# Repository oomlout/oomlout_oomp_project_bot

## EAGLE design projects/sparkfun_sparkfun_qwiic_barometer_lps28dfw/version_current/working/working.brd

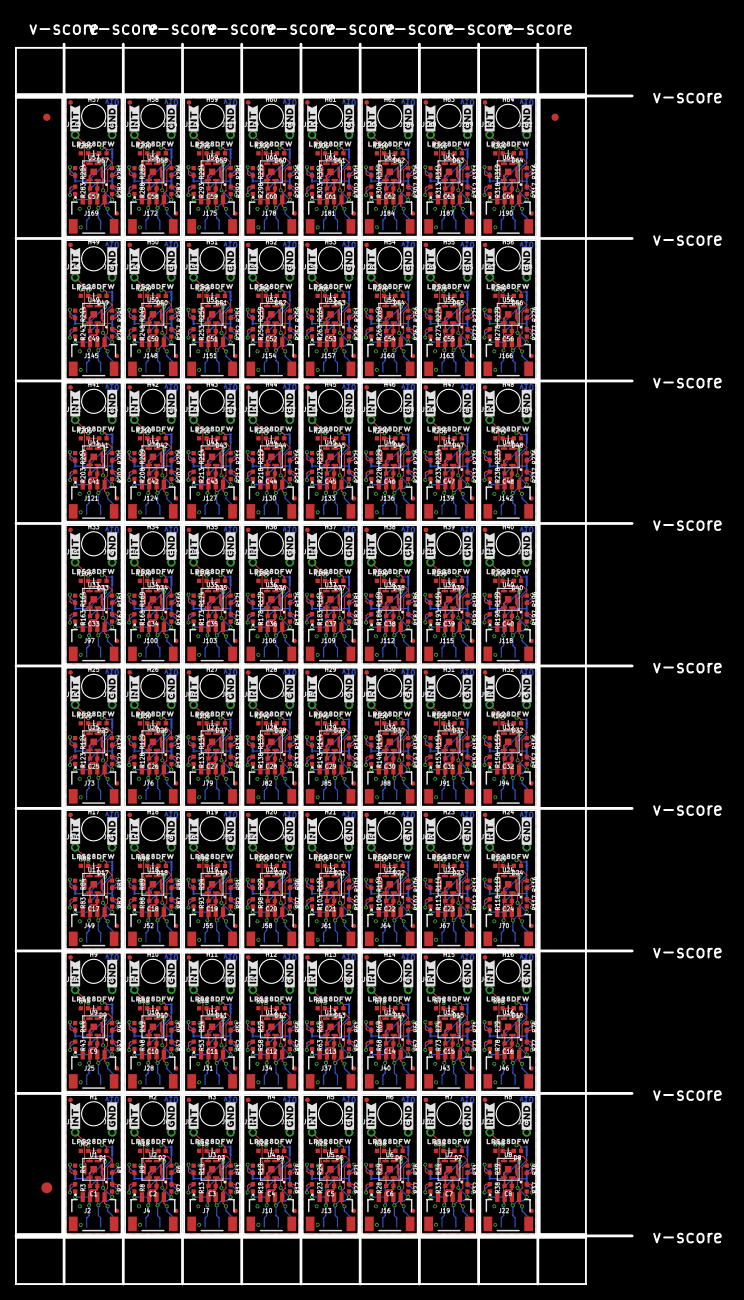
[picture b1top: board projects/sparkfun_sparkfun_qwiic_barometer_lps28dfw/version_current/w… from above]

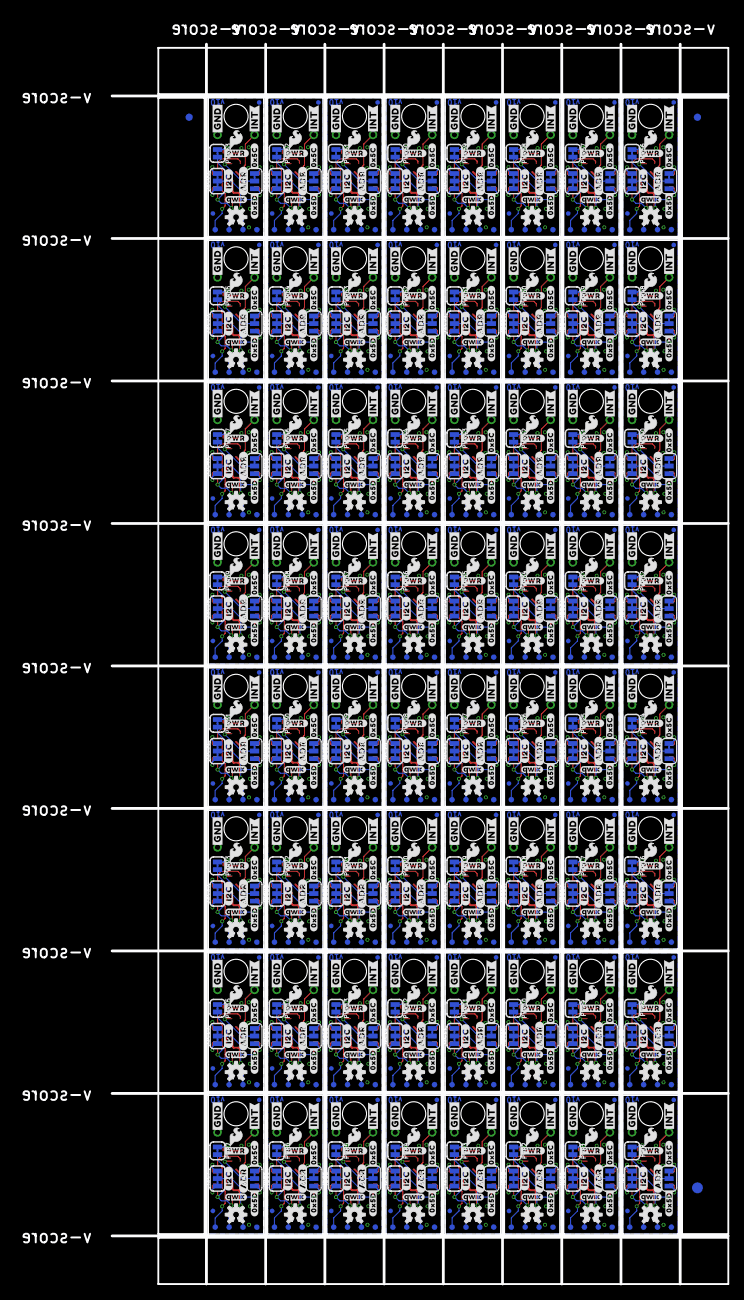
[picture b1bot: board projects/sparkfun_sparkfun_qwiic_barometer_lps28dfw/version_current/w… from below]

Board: 2 copper layers, 84.6 x 170.2 mm, 2438 parts (1219 on the bottom side), 768 nets.

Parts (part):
ADR, ADR1, ADR2, ADR3, ADR4, ADR5, ADR6, ADR7, ADR8, ADR9, ADR10, ADR11, ADR12, ADR13, ADR14, ADR15, ADR16, ADR17, ADR18, ADR19, ADR20, ADR21, ADR22, ADR23, ADR24, ADR25, ADR26, ADR27, ADR28, ADR29, ADR30, ADR31, ADR32, ADR33, ADR34, ADR35, ADR36, ADR37, ADR38, ADR39, ADR40, ADR41, ADR42, ADR43, ADR44, ADR45, ADR46, ADR47, ADR48, ADR49, ADR50, ADR51, ADR52, ADR53, ADR54, ADR55, ADR56, ADR57, ADR58, ADR59, ADR60, ADR61, ADR62, ADR63: JUMPER-SMT_3_1-NC_TRACE_SILK; SMT-JUMPER_3_1-NC_TRACE_SILK
C1, C2, C3, C4, C5, C6, C7, C8, C9, C10, C11, C12, C13, C14, C15, C16, C17, C18, C19, C20, C21, C22, C23, C24, C25, C26, C27, C28, C29, C30, C31, C32, C33, C34, C35, C36, C37, C38, C39, C40, C41, C42, C43, C44, C45, C46, C47, C48, C49, C50, C51, C52, C53, C54, C55, C56, C57, C58, C59, C60, C61, C62, C63, C64: 0.1uF; 0402-TIGHT
D1, D2, D3, D4, D5, D6, D7, D8, D9, D10, D11, D12, D13, D14, D15, D16, D17, D18, D19, D20, D21, D22, D23, D24, D25, D26, D27, D28, D29, D30, D31, D32, D33, D34, D35, D36, D37, D38, D39, D40, D41, D42, D43, D44, D45, D46, D47, D48, D49, D50, D51, D52, D53, D54, D55, D56, D57, D58, D59, D60, D61, D62, D63, D64: RED; LED-0402
E$1, E$2, E$3, E$4: FIDUCIAL-1X2
E$5, E$6: FIDUCIAL-1.5X3
FD1, FD2, FD3, FD4, FD5, FD6, FD7, FD8, FD9, FD10, FD11, FD12, FD13, FD14, FD15, FD16, FD17, FD18, FD19, FD20, FD21, FD22, FD23, FD24, FD25, FD26, FD27, FD28, FD29, FD30, FD31, FD32, FD33, FD34, FD35, FD36, FD37, FD38, FD39, FD40, FD41, FD42, FD43, FD44, FD45, FD46, FD47, FD48, FD49, FD50, FD51, FD52, FD53, FD54, FD55, FD56, FD57, FD58, FD59, FD60, FD61, FD62, FD63, FD64, FD65, FD66, FD67, FD68, FD69, FD70, FD71, FD72, FD73, FD74, FD75, FD76, FD77, FD78, FD79, FD80, FD81, FD82, FD83, FD84, FD85, FD86, FD87, FD88, FD89, FD90, FD91, FD92, FD93, FD94, FD95, FD96, FD97, FD98, FD99, FD100, FD101, FD102, FD103, FD104, FD105, FD106, FD107, FD108, FD109, FD110, FD111, FD112, FD113, FD114, FD115, FD116, FD117, FD118, FD119, FD120, FD121, FD122, FD123, FD124, FD125, FD126, FD127, FD128, FD129, FD130, FD131, FD132, FD133, FD134, FD135, FD136, FD137, FD138, FD139, FD140, FD141, FD142, FD143, FD144, FD145, FD146, FD147, FD148, FD149, FD150, FD151, FD152, FD153, FD154, FD155, FD156, FD157, FD158, FD159, FD160, FD161, FD162, FD163, FD164, FD165, FD166, FD167, FD168, FD169, FD170, FD171, FD172, FD173, FD174, FD175, FD176, FD177, FD178, FD179, FD180, FD181, FD182, FD183, FD184, FD185, FD186, FD187, FD188, FD189, FD190, FD191, FD192, FD193, FD194, FD195, FD196, FD197, FD198, FD199, FD200, FD201, FD202, FD203, FD204, FD205, FD206, FD207, FD208, FD209, FD210, FD211, FD212, FD213, FD214, FD215, FD216, FD217, FD218, FD219, FD220, FD221, FD222, FD223, FD224, FD225, FD226, FD227, FD228, FD229, FD230, FD231, FD232, FD233, FD234, FD235, FD236, FD237, FD238, FD239, FD240, FD241, FD242, FD243, FD244, FD245, FD246, FD247, FD248, FD249, FD250, FD251, FD252, FD253, FD254, FD255, FD256: FIDUCIALUFIDUCIAL; FIDUCIAL-MICRO
FRAME1, FRAME2, FRAME3, FRAME4, FRAME5, FRAME6, FRAME7, FRAME8, FRAME9, FRAME10, FRAME11, FRAME12, FRAME13, FRAME14, FRAME15, FRAME16, FRAME17, FRAME18, FRAME19, FRAME20, FRAME21, FRAME22, FRAME23, FRAME24, FRAME25, FRAME26, FRAME27, FRAME28, FRAME29, FRAME30, FRAME31, FRAME32, FRAME33, FRAME34, FRAME35, FRAME36, FRAME37, FRAME38, FRAME39, FRAME40, FRAME41, FRAME42, FRAME43, FRAME44, FRAME45, FRAME46, FRAME47, FRAME48, FRAME49, FRAME50, FRAME51, FRAME52, FRAME53, FRAME54, FRAME55, FRAME56, FRAME57, FRAME58, FRAME59, FRAME60, FRAME61, FRAME62, FRAME63, FRAME64: FRAME-LETTER; CREATIVE_COMMONS
H1, H2, H3, H4, H5, H6, H7, H8, H9, H10, H11, H12, H13, H14, H15, H16, H17, H18, H19, H20, H21, H22, H23, H24, H25, H26, H27, H28, H29, H30, H31, H32, H33, H34, H35, H36, H37, H38, H39, H40, H41, H42, H43, H44, H45, H46, H47, H48, H49, H50, H51, H52, H53, H54, H55, H56, H57, H58, H59, H60, H61, H62, H63, H64: STAND-OFF
I2C, I2C1, I2C2, I2C3, I2C4, I2C5, I2C6, I2C7, I2C8, I2C9, I2C10, I2C11, I2C12, I2C13, I2C14, I2C15, I2C16, I2C17, I2C18, I2C19, I2C20, I2C21, I2C22, I2C23, I2C24, I2C25, I2C26, I2C27, I2C28, I2C29, I2C30, I2C31, I2C32, I2C33, I2C34, I2C35, I2C36, I2C37, I2C38, I2C39, I2C40, I2C41, I2C42, I2C43, I2C44, I2C45, I2C46, I2C47, I2C48, I2C49, I2C50, I2C51, I2C52, I2C53, I2C54, I2C55, I2C56, I2C57, I2C58, I2C59, I2C60, I2C61, I2C62, I2C63: JUMPER-SMT_3_2-NC_TRACE_SILK; SMT-JUMPER_3_2-NC_TRACE_SILK
J1, J3, J5, J6, J8, J9, J11, J12, J14, J15, J17, J18, J20, J21, J23, J24, J26, J27, J29, J30, J32, J33, J35, J36, J38, J39, J41, J42, J44, J45, J47, J48, J50, J51, J53, J54, J56, J57, J59, J60, J62, J63, J65, J66, J68, J69, J71, J72, J74, J75, J77, J78, J80, J81, J83, J84, J86, J87, J89, J90, J92, J93, J95, J96, J98, J99, J101, J102, J104, J105, J107, J108, J110, J111, J113, J114, J116, J117, J119, J120, J122, J123, J125, J126, J128, J129, J131, J132, J134, J135, J137, J138, J140, J141, J143, J144, J146, J147, J149, J150, J152, J153, J155, J156, J158, J159, J161, J162, J164, J165, J167, J168, J170, J171, J173, J174, J176, J177, J179, J180, J182, J183, J185, J186, J188, J189, J191, J192: 1X01_1MM_NO_SILK
J2, J4, J7, J10, J13, J16, J19, J22, J25, J28, J31, J34, J37, J40, J43, J46, J49, J52, J55, J58, J61, J64, J67, J70, J73, J76, J79, J82, J85, J88, J91, J94, J97, J100, J103, J106, J109, J112, J115, J118, J121, J124, J127, J130, J133, J136, J139, J142, J145, J148, J151, J154, J157, J160, J163, J166, J169, J172, J175, J178, J181, J184, J187, J190: QWIIC_RIGHT_ANGLE; JST04_1MM_RA
LOGO1, LOGO4, LOGO7, LOGO10, LOGO13, LOGO16, LOGO19, LOGO22, LOGO25, LOGO28, LOGO31, LOGO34, LOGO37, LOGO40, LOGO43, LOGO46, LOGO49, LOGO52, LOGO55, LOGO58, LOGO61, LOGO64, LOGO67, LOGO70, LOGO73, LOGO76, LOGO79, LOGO82, LOGO85, LOGO88, LOGO91, LOGO94, LOGO97, LOGO100, LOGO103, LOGO106, LOGO109, LOGO112, LOGO115, LOGO118, LOGO121, LOGO124, LOGO127, LOGO130, LOGO133, LOGO136, LOGO139, LOGO142, LOGO145, LOGO148, LOGO151, LOGO154, LOGO157, LOGO160, LOGO163, LOGO166, LOGO169, LOGO172, LOGO175, LOGO178, LOGO181, LOGO184, LOGO187, LOGO190: OSHW-LOGOS; OSHW-LOGO-S
LOGO2, LOGO5, LOGO8, LOGO11, LOGO14, LOGO17, LOGO20, LOGO23, LOGO26, LOGO29, LOGO32, LOGO35, LOGO38, LOGO41, LOGO44, LOGO47, LOGO50, LOGO53, LOGO56, LOGO59, LOGO62, LOGO65, LOGO68, LOGO71, LOGO74, LOGO77, LOGO80, LOGO83, LOGO86, LOGO89, LOGO92, LOGO95, LOGO98, LOGO101, LOGO104, LOGO107, LOGO110, LOGO113, LOGO116, LOGO119, LOGO122, LOGO125, LOGO128, LOGO131, LOGO134, LOGO137, LOGO140, LOGO143, LOGO146, LOGO149, LOGO152, LOGO155, LOGO158, LOGO161, LOGO164, LOGO167, LOGO170, LOGO173, LOGO176, LOGO179, LOGO182, LOGO185, LOGO188, LOGO191: QWIIC_LOGO_3MM; QWIIC_3MM
LOGO3, LOGO6, LOGO9, LOGO12, LOGO15, LOGO18, LOGO21, LOGO24, LOGO27, LOGO30, LOGO33, LOGO36, LOGO39, LOGO42, LOGO45, LOGO48, LOGO51, LOGO54, LOGO57, LOGO60, LOGO63, LOGO66, LOGO69, LOGO72, LOGO75, LOGO78, LOGO81, LOGO84, LOGO87, LOGO90, LOGO93, LOGO96, LOGO99, LOGO102, LOGO105, LOGO108, LOGO111, LOGO114, LOGO117, LOGO120, LOGO123, LOGO126, LOGO129, LOGO132, LOGO135, LOGO138, LOGO141, LOGO144, LOGO147, LOGO150, LOGO153, LOGO156, LOGO159, LOGO162, LOGO165, LOGO168, LOGO171, LOGO174, LOGO177, LOGO180, LOGO183, LOGO186, LOGO189, LOGO192: SFE_LOGO_NAME_FLAMEBLANK; BLANK
PWR, PWR1, PWR2, PWR3, PWR4, PWR5, PWR6, PWR7, PWR8, PWR9, PWR10, PWR11, PWR12, PWR13, PWR14, PWR15, PWR16, PWR17, PWR18, PWR19, PWR20, PWR21, PWR22, PWR23, PWR24, PWR25, PWR26, PWR27, PWR28, PWR29, PWR30, PWR31, PWR32, PWR33, PWR34, PWR35, PWR36, PWR37, PWR38, PWR39, PWR40, PWR41, PWR42, PWR43, PWR44, PWR45, PWR46, PWR47, PWR48, PWR49, PWR50, PWR51, PWR52, PWR53, PWR54, PWR55, PWR56, PWR57, PWR58, PWR59, PWR60, PWR61, PWR62, PWR63: JUMPER-SMT_2_NC_TRACE_SILK; SMT-JUMPER_2_NC_TRACE_SILK
R1, R2, R5, R6, R7, R10, R11, R12, R15, R16, R17, R20, R21, R22, R25, R26, R27, R30, R31, R32, R35, R36, R37, R40, R41, R42, R45, R46, R47, R50, R51, R52, R55, R56, R57, R60, R61, R62, R65, R66, R67, R70, R71, R72, R75, R76, R77, R80, R81, R82, R85, R86, R87, R90, R91, R92, R95, R96, R97, R100, R101, R102, R105, R106, R107, R110, R111, R112, R115, R116, R117, R120, R121, R122, R125, R126, R127, R130, R131, R132, R135, R136, R137, R140, R141, R142, R145, R146, R147, R150, R151, R152, R155, R156, R157, R160, R161, R162, R165, R166, R167, R170, R171, R172, R175, R176, R177, R180, R181, R182, R185, R186, R187, R190, R191, R192, R195, R196, R197, R200, R201, R202, R205, R206, R207, R210, R211, R212, R215, R216, R217, R220, R221, R222, R225, R226, R227, R230, R231, R232, R235, R236, R237, R240, R241, R242, R245, R246, R247, R250, R251, R252, R255, R256, R257, R260, R261, R262, R265, R266, R267, R270, R271, R272, R275, R276, R277, R280, R281, R282, R285, R286, R287, R290, R291, R292, R295, R296, R297, R300, R301, R302, R305, R306, R307, R310, R311, R312, R315, R316, R317, R320: 2.2k; 0402-TIGHT
R3, R4, R8, R9, R13, R14, R18, R19, R23, R24, R28, R29, R33, R34, R38, R39, R43, R44, R48, R49, R53, R54, R58, R59, R63, R64, R68, R69, R73, R74, R78, R79, R83, R84, R88, R89, R93, R94, R98, R99, R103, R104, R108, R109, R113, R114, R118, R119, R123, R124, R128, R129, R133, R134, R138, R139, R143, R144, R148, R149, R153, R154, R158, R159, R163, R164, R168, R169, R173, R174, R178, R179, R183, R184, R188, R189, R193, R194, R198, R199, R203, R204, R208, R209, R213, R214, R218, R219, R223, R224, R228, R229, R233, R234, R238, R239, R243, R244, R248, R249, R253, R254, R258, R259, R263, R264, R268, R269, R273, R274, R278, R279, R283, R284, R288, R289, R293, R294, R298, R299, R303, R304, R308, R309, R313, R314, R318, R319: 10k; 0402-TIGHT
TP1, TP2, TP3, TP4, TP5, TP6, TP7, TP8, TP9, TP10, TP11, TP12, TP13, TP14, TP15, TP16, TP17, TP18, TP19, TP20, TP21, TP22, TP23, TP24, TP25, TP26, TP27, TP28, TP29, TP30, TP31, TP32, TP33, TP34, TP35, TP36, TP37, TP38, TP39, TP40, TP41, TP42, TP43, TP44, TP45, TP46, TP47, TP48, TP49, TP50, TP51, TP52, TP53, TP54, TP55, TP56, TP57, TP58, TP59, TP60, TP61, TP62, TP63, TP64, TP65, TP66, TP67, TP68, TP69, TP70, TP71, TP72, TP73, TP74, TP75, TP76, TP77, TP78, TP79, TP80, TP81, TP82, TP83, TP84, TP85, TP86, TP87, TP88, TP89, TP90, TP91, TP92, TP93, TP94, TP95, TP96, TP97, TP98, TP99, TP100, TP101, TP102, TP103, TP104, TP105, TP106, TP107, TP108, TP109, TP110, TP111, TP112, TP113, TP114, TP115, TP116, TP117, TP118, TP119, TP120, TP121, TP122, TP123, TP124, TP125, TP126, TP127, TP128, TP129, TP130, TP131, TP132, TP133, TP134, TP135, TP136, TP137, TP138, TP139, TP140, TP141, TP142, TP143, TP144, TP145, TP146, TP147, TP148, TP149, TP150, TP151, TP152, TP153, TP154, TP155, TP156, TP157, TP158, TP159, TP160, TP161, TP162, TP163, TP164, TP165, TP166, TP167, TP168, TP169, TP170, TP171, TP172, TP173, TP174, TP175, TP176, TP177, TP178, TP179, TP180, TP181, TP182, TP183, TP184, TP185, TP186, TP187, TP188, TP189, TP190, TP191, TP192, TP193, TP194, TP195, TP196, TP197, TP198, TP199, TP200, TP201, TP202, TP203, TP204, TP205, TP206, TP207, TP208, TP209, TP210, TP211, TP212, TP213, TP214, TP215, TP216, TP217, TP218, TP219, TP220, TP221, TP222, TP223, TP224, TP225, TP226, TP227, TP228, TP229, TP230, TP231, TP232, TP233, TP234, TP235, TP236, TP237, TP238, TP239, TP240, TP241, TP242, TP243, TP244, TP245, TP246, TP247, TP248, TP249, TP250, TP251, TP252, TP253, TP254, TP255, TP256: TEST-POINT3; PAD.03X.03
U1, U2, U3, U4, U5, U6, U7, U8, U9, U10, U11, U12, U13, U14, U15, U16, U17, U18, U19, U20, U21, U22, U23, U24, U25, U26, U27, U28, U29, U30, U31, U32, U33, U34, U35, U36, U37, U38, U39, U40, U41, U42, U43, U44, U45, U46, U47, U48, U49, U50, U51, U52, U53, U54, U55, U56, U57, U58, U59, U60, U61, U62, U63, U64: LPS28DFW
U$1, U$3, U$15, U$19, U$28, U$30, U$39, U$41, U$50, U$52, U$61, U$63, U$72, U$74, U$83, U$85, U$94, U$96, U$105, U$107, U$116, U$118, U$127, U$129, U$138, U$140, U$149, U$151, U$160, U$162, U$171, U$173, U$182, U$184, U$193, U$195, U$204, U$206, U$215, U$217, U$226, U$228, U$237, U$239, U$248, U$250, U$259, U$261, U$270, U$272, U$281, U$283, U$292, U$294, U$303, U$305, U$314, U$316, U$325, U$327, U$336, U$338, U$347, U$349, U$358, U$360, U$369, U$371, U$380, U$382, U$391, U$393, U$402, U$404, U$413, U$415, U$424, U$426, U$435, U$437, U$446, U$448, U$457, U$459, U$468, U$470, U$479, U$481, U$490, U$492, U$501, U$503, U$512, U$514, U$523, U$525, U$534, U$536, U$545, U$547, U$556, U$558, U$567, U$569, U$578, U$580, U$589, U$591, U$600, U$602, U$611, U$613, U$622, U$624, U$633, U$635, U$644, U$646, U$655, U$657, U$666, U$668, U$677, U$679, U$688, U$690, U$699, U$701: #INT#0
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
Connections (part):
3.3V: C1.1, I2C.2, J2.2, PWR.2, R3.2, TP2.1, U1.6
3.3V1: C2.1, I2C1.2, J4.2, PWR1.2, R8.2, TP6.1, U2.6
3.3V2: C3.1, I2C2.2, J7.2, PWR2.2, R13.2, TP10.1, U3.6
3.3V3: C4.1, I2C3.2, J10.2, PWR3.2, R18.2, TP14.1, U4.6
3.3V4: C5.1, I2C4.2, J13.2, PWR4.2, R23.2, TP18.1, U5.6
3.3V5: C6.1, I2C5.2, J16.2, PWR5.2, R28.2, TP22.1, U6.6
3.3V6: C7.1, I2C6.2, J19.2, PWR6.2, R33.2, TP26.1, U7.6
3.3V7: C8.1, I2C7.2, J22.2, PWR7.2, R38.2, TP30.1, U8.6
3.3V8: C9.1, I2C8.2, J25.2, PWR8.2, R43.2, TP34.1, U9.6
3.3V9: C10.1, I2C9.2, J28.2, PWR9.2, R48.2, TP38.1, U10.6
3.3V10: C11.1, I2C10.2, J31.2, PWR10.2, R53.2, TP42.1, U11.6
3.3V11: C12.1, I2C11.2, J34.2, PWR11.2, R58.2, TP46.1, U12.6
3.3V12: C13.1, I2C12.2, J37.2, PWR12.2, R63.2, TP50.1, U13.6
3.3V13: C14.1, I2C13.2, J40.2, PWR13.2, R68.2, TP54.1, U14.6
3.3V14: C15.1, I2C14.2, J43.2, PWR14.2, R73.2, TP58.1, U15.6
3.3V15: C16.1, I2C15.2, J46.2, PWR15.2, R78.2, TP62.1, U16.6
3.3V16: C17.1, I2C16.2, J49.2, PWR16.2, R83.2, TP66.1, U17.6
3.3V17: C18.1, I2C17.2, J52.2, PWR17.2, R88.2, TP70.1, U18.6
3.3V18: C19.1, I2C18.2, J55.2, PWR18.2, R93.2, TP74.1, U19.6
3.3V19: C20.1, I2C19.2, J58.2, PWR19.2, R98.2, TP78.1, U20.6
3.3V20: C21.1, I2C20.2, J61.2, PWR20.2, R103.2, TP82.1, U21.6
3.3V21: C22.1, I2C21.2, J64.2, PWR21.2, R108.2, TP86.1, U22.6
3.3V22: C23.1, I2C22.2, J67.2, PWR22.2, R113.2, TP90.1, U23.6
3.3V23: C24.1, I2C23.2, J70.2, PWR23.2, R118.2, TP94.1, U24.6
3.3V24: C25.1, I2C24.2, J73.2, PWR24.2, R123.2, TP98.1, U25.6
3.3V25: C26.1, I2C25.2, J76.2, PWR25.2, R128.2, TP102.1, U26.6
3.3V26: C27.1, I2C26.2, J79.2, PWR26.2, R133.2, TP106.1, U27.6
3.3V27: C28.1, I2C27.2, J82.2, PWR27.2, R138.2, TP110.1, U28.6
3.3V28: C29.1, I2C28.2, J85.2, PWR28.2, R143.2, TP114.1, U29.6
3.3V29: C30.1, I2C29.2, J88.2, PWR29.2, R148.2, TP118.1, U30.6
3.3V30: C31.1, I2C30.2, J91.2, PWR30.2, R153.2, TP122.1, U31.6
3.3V31: C32.1, I2C31.2, J94.2, PWR31.2, R158.2, TP126.1, U32.6
3.3V32: C33.1, I2C32.2, J97.2, PWR32.2, R163.2, TP130.1, U33.6
3.3V33: C34.1, I2C33.2, J100.2, PWR33.2, R168.2, TP134.1, U34.6
3.3V34: C35.1, I2C34.2, J103.2, PWR34.2, R173.2, TP138.1, U35.6
3.3V35: C36.1, I2C35.2, J106.2, PWR35.2, R178.2, TP142.1, U36.6
3.3V36: C37.1, I2C36.2, J109.2, PWR36.2, R183.2, TP146.1, U37.6
3.3V37: C38.1, I2C37.2, J112.2, PWR37.2, R188.2, TP150.1, U38.6
3.3V38: C39.1, I2C38.2, J115.2, PWR38.2, R193.2, TP154.1, U39.6
3.3V39: C40.1, I2C39.2, J118.2, PWR39.2, R198.2, TP158.1, U40.6
3.3V40: C41.1, I2C40.2, J121.2, PWR40.2, R203.2, TP162.1, U41.6
3.3V41: C42.1, I2C41.2, J124.2, PWR41.2, R208.2, TP166.1, U42.6
3.3V42: C43.1, I2C42.2, J127.2, PWR42.2, R213.2, TP170.1, U43.6
3.3V43: C44.1, I2C43.2, J130.2, PWR43.2, R218.2, TP174.1, U44.6
3.3V44: C45.1, I2C44.2, J133.2, PWR44.2, R223.2, TP178.1, U45.6
3.3V45: C46.1, I2C45.2, J136.2, PWR45.2, R228.2, TP182.1, U46.6
3.3V46: C47.1, I2C46.2, J139.2, PWR46.2, R233.2, TP186.1, U47.6
3.3V47: C48.1, I2C47.2, J142.2, PWR47.2, R238.2, TP190.1, U48.6
3.3V48: C49.1, I2C48.2, J145.2, PWR48.2, R243.2, TP194.1, U49.6
3.3V49: C50.1, I2C49.2, J148.2, PWR49.2, R248.2, TP198.1, U50.6
3.3V50: C51.1, I2C50.2, J151.2, PWR50.2, R253.2, TP202.1, U51.6
3.3V51: C52.1, I2C51.2, J154.2, PWR51.2, R258.2, TP206.1, U52.6
3.3V52: C53.1, I2C52.2, J157.2, PWR52.2, R263.2, TP210.1, U53.6
3.3V53: C54.1, I2C53.2, J160.2, PWR53.2, R268.2, TP214.1, U54.6
3.3V54: C55.1, I2C54.2, J163.2, PWR54.2, R273.2, TP218.1, U55.6
3.3V55: C56.1, I2C55.2, J166.2, PWR55.2, R278.2, TP222.1, U56.6
3.3V56: C57.1, I2C56.2, J169.2, PWR56.2, R283.2, TP226.1, U57.6
3.3V57: C58.1, I2C57.2, J172.2, PWR57.2, R288.2, TP230.1, U58.6
3.3V58: C59.1, I2C58.2, J175.2, PWR58.2, R293.2, TP234.1, U59.6
3.3V59: C60.1, I2C59.2, J178.2, PWR59.2, R298.2, TP238.1, U60.6
3.3V60: C61.1, I2C60.2, J181.2, PWR60.2, R303.2, TP242.1, U61.6
3.3V61: C62.1, I2C61.2, J184.2, PWR61.2, R308.2, TP246.1, U62.6
3.3V62: C63.1, I2C62.2, J187.2, PWR62.2, R313.2, TP250.1, U63.6
3.3V63: C64.1, I2C63.2, J190.2, PWR63.2, R318.2, TP254.1, U64.6
ADR: ADR.2, U1.2
ADR1: ADR1.2, U2.2
ADR2: ADR2.2, U3.2
ADR3: ADR3.2, U4.2
ADR4: ADR4.2, U5.2
ADR5: ADR5.2, U6.2
ADR6: ADR6.2, U7.2
ADR7: ADR7.2, U8.2
ADR8: ADR8.2, U9.2
ADR9: ADR9.2, U10.2
ADR10: ADR10.2, U11.2
ADR11: ADR11.2, U12.2
ADR12: ADR12.2, U13.2
ADR13: ADR13.2, U14.2
ADR14: ADR14.2, U15.2
ADR15: ADR15.2, U16.2
ADR16: ADR16.2, U17.2
ADR17: ADR17.2, U18.2
ADR18: ADR18.2, U19.2
ADR19: ADR19.2, U20.2
ADR20: ADR20.2, U21.2
ADR21: ADR21.2, U22.2
ADR22: ADR22.2, U23.2
ADR23: ADR23.2, U24.2
ADR24: ADR24.2, U25.2
ADR25: ADR25.2, U26.2
ADR26: ADR26.2, U27.2
ADR27: ADR27.2, U28.2
ADR28: ADR28.2, U29.2
ADR29: ADR29.2, U30.2
ADR30: ADR30.2, U31.2
ADR31: ADR31.2, U32.2
ADR32: ADR32.2, U33.2
ADR33: ADR33.2, U34.2
ADR34: ADR34.2, U35.2
ADR35: ADR35.2, U36.2
ADR36: ADR36.2, U37.2
ADR37: ADR37.2, U38.2
ADR38: ADR38.2, U39.2
ADR39: ADR39.2, U40.2
ADR40: ADR40.2, U41.2
ADR41: ADR41.2, U42.2
ADR42: ADR42.2, U43.2
ADR43: ADR43.2, U44.2
ADR44: ADR44.2, U45.2
ADR45: ADR45.2, U46.2
ADR46: ADR46.2, U47.2
ADR47: ADR47.2, U48.2
ADR48: ADR48.2, U49.2
ADR49: ADR49.2, U50.2
ADR50: ADR50.2, U51.2
ADR51: ADR51.2, U52.2
ADR52: ADR52.2, U53.2
ADR53: ADR53.2, U54.2
ADR54: ADR54.2, U55.2
ADR55: ADR55.2, U56.2
ADR56: ADR56.2, U57.2
ADR57: ADR57.2, U58.2
ADR58: ADR58.2, U59.2
ADR59: ADR59.2, U60.2
ADR60: ADR60.2, U61.2
ADR61: ADR61.2, U62.2
ADR62: ADR62.2, U63.2
ADR63: ADR63.2, U64.2
GND: C1.2, J1.1, J2.1, R4.1, R5.1, TP1.1, U1.5, U1.7
GND1: C2.2, J4.1, J6.1, R9.1, R10.1, TP5.1, U2.5, U2.7
GND2: C3.2, J7.1, J9.1, R14.1, R15.1, TP9.1, U3.5, U3.7
GND3: C4.2, J10.1, J12.1, R19.1, R20.1, TP13.1, U4.5, U4.7
GND4: C5.2, J13.1, J15.1, R24.1, R25.1, TP17.1, U5.5, U5.7
GND5: C6.2, J16.1, J18.1, R29.1, R30.1, TP21.1, U6.5, U6.7
GND6: C7.2, J19.1, J21.1, R34.1, R35.1, TP25.1, U7.5, U7.7
GND7: C8.2, J22.1, J24.1, R39.1, R40.1, TP29.1, U8.5, U8.7
GND8: C9.2, J25.1, J27.1, R44.1, R45.1, TP33.1, U9.5, U9.7
GND9: C10.2, J28.1, J30.1, R49.1, R50.1, TP37.1, U10.5, U10.7
GND10: C11.2, J31.1, J33.1, R54.1, R55.1, TP41.1, U11.5, U11.7
GND11: C12.2, J34.1, J36.1, R59.1, R60.1, TP45.1, U12.5, U12.7
GND12: C13.2, J37.1, J39.1, R64.1, R65.1, TP49.1, U13.5, U13.7
GND13: C14.2, J40.1, J42.1, R69.1, R70.1, TP53.1, U14.5, U14.7
GND14: C15.2, J43.1, J45.1, R74.1, R75.1, TP57.1, U15.5, U15.7
GND15: C16.2, J46.1, J48.1, R79.1, R80.1, TP61.1, U16.5, U16.7
GND16: C17.2, J49.1, J51.1, R84.1, R85.1, TP65.1, U17.5, U17.7
GND17: C18.2, J52.1, J54.1, R89.1, R90.1, TP69.1, U18.5, U18.7
GND18: C19.2, J55.1, J57.1, R94.1, R95.1, TP73.1, U19.5, U19.7
GND19: C20.2, J58.1, J60.1, R99.1, R100.1, TP77.1, U20.5, U20.7
GND20: C21.2, J61.1, J63.1, R104.1, R105.1, TP81.1, U21.5, U21.7
GND21: C22.2, J64.1, J66.1, R109.1, R110.1, TP85.1, U22.5, U22.7
GND22: C23.2, J67.1, J69.1, R114.1, R115.1, TP89.1, U23.5, U23.7
GND23: C24.2, J70.1, J72.1, R119.1, R120.1, TP93.1, U24.5, U24.7
GND24: C25.2, J73.1, J75.1, R124.1, R125.1, TP97.1, U25.5, U25.7
GND25: C26.2, J76.1, J78.1, R129.1, R130.1, TP101.1, U26.5, U26.7
GND26: C27.2, J79.1, J81.1, R134.1, R135.1, TP105.1, U27.5, U27.7
GND27: C28.2, J82.1, J84.1, R139.1, R140.1, TP109.1, U28.5, U28.7
GND28: C29.2, J85.1, J87.1, R144.1, R145.1, TP113.1, U29.5, U29.7
GND29: C30.2, J88.1, J90.1, R149.1, R150.1, TP117.1, U30.5, U30.7
GND30: C31.2, J91.1, J93.1, R154.1, R155.1, TP121.1, U31.5, U31.7
GND31: C32.2, J94.1, J96.1, R159.1, R160.1, TP125.1, U32.5, U32.7
GND32: C33.2, J97.1, J99.1, R164.1, R165.1, TP129.1, U33.5, U33.7
GND33: C34.2, J100.1, J102.1, R169.1, R170.1, TP133.1, U34.5, U34.7
GND34: C35.2, J103.1, J105.1, R174.1, R175.1, TP137.1, U35.5, U35.7
GND35: C36.2, J106.1, J108.1, R179.1, R180.1, TP141.1, U36.5, U36.7
GND36: C37.2, J109.1, J111.1, R184.1, R185.1, TP145.1, U37.5, U37.7
GND37: C38.2, J112.1, J114.1, R189.1, R190.1, TP149.1, U38.5, U38.7
GND38: C39.2, J115.1, J117.1, R194.1, R195.1, TP153.1, U39.5, U39.7
GND39: C40.2, J118.1, J120.1, R199.1, R200.1, TP157.1, U40.5, U40.7
GND40: C41.2, J121.1, J123.1, R204.1, R205.1, TP161.1, U41.5, U41.7
GND41: C42.2, J124.1, J126.1, R209.1, R210.1, TP165.1, U42.5, U42.7
GND42: C43.2, J127.1, J129.1, R214.1, R215.1, TP169.1, U43.5, U43.7
GND43: C44.2, J130.1, J132.1, R219.1, R220.1, TP173.1, U44.5, U44.7
GND44: C45.2, J133.1, J135.1, R224.1, R225.1, TP177.1, U45.5, U45.7
GND45: C46.2, J136.1, J138.1, R229.1, R230.1, TP181.1, U46.5, U46.7
GND46: C47.2, J139.1, J141.1, R234.1, R235.1, TP185.1, U47.5, U47.7
GND47: C48.2, J142.1, J144.1, R239.1, R240.1, TP189.1, U48.5, U48.7
GND48: C49.2, J145.1, J147.1, R244.1, R245.1, TP193.1, U49.5, U49.7
GND49: C50.2, J148.1, J150.1, R249.1, R250.1, TP197.1, U50.5, U50.7
GND50: C51.2, J151.1, J153.1, R254.1, R255.1, TP201.1, U51.5, U51.7
GND51: C52.2, J154.1, J156.1, R259.1, R260.1, TP205.1, U52.5, U52.7
GND52: C53.2, J157.1, J159.1, R264.1, R265.1, TP209.1, U53.5, U53.7
GND53: C54.2, J160.1, J162.1, R269.1, R270.1, TP213.1, U54.5, U54.7
GND54: C55.2, J163.1, J165.1, R274.1, R275.1, TP217.1, U55.5, U55.7
GND55: C56.2, J166.1, J168.1, R279.1, R280.1, TP221.1, U56.5, U56.7
GND56: C57.2, J169.1, J171.1, R284.1, R285.1, TP225.1, U57.5, U57.7
GND57: C58.2, J172.1, J174.1, R289.1, R290.1, TP229.1, U58.5, U58.7
GND58: C59.2, J175.1, J177.1, R294.1, R295.1, TP233.1, U59.5, U59.7
GND59: C60.2, J178.1, J180.1, R299.1, R300.1, TP237.1, U60.5, U60.7
GND60: C61.2, J181.1, J183.1, R304.1, R305.1, TP241.1, U61.5, U61.7
GND61: C62.2, J184.1, J186.1, R309.1, R310.1, TP245.1, U62.5, U62.7
GND62: C63.2, J187.1, J189.1, R314.1, R315.1, TP249.1, U63.5, U63.7
GND63: C64.2, J190.1, J192.1, R319.1, R320.1, TP253.1, U64.5, U64.7
INT: J3.1, U1.4
INT1: J5.1, U2.4
INT2: J8.1, U3.4
INT3: J11.1, U4.4
INT4: J14.1, U5.4
INT5: J17.1, U6.4
INT6: J20.1, U7.4
INT7: J23.1, U8.4
INT8: J26.1, U9.4
INT9: J29.1, U10.4
INT10: J32.1, U11.4
INT11: J35.1, U12.4
INT12: J38.1, U13.4
INT13: J41.1, U14.4
INT14: J44.1, U15.4
INT15: J47.1, U16.4
INT16: J50.1, U17.4
INT17: J53.1, U18.4
INT18: J56.1, U19.4
INT19: J59.1, U20.4
INT20: J62.1, U21.4
INT21: J65.1, U22.4
INT22: J68.1, U23.4
INT23: J71.1, U24.4
INT24: J74.1, U25.4
INT25: J77.1, U26.4
INT26: J80.1, U27.4
INT27: J83.1, U28.4
INT28: J86.1, U29.4
INT29: J89.1, U30.4
INT30: J92.1, U31.4
INT31: J95.1, U32.4
INT32: J98.1, U33.4
INT33: J101.1, U34.4
INT34: J104.1, U35.4
INT35: J107.1, U36.4
INT36: J110.1, U37.4
INT37: J113.1, U38.4
INT38: J116.1, U39.4
INT39: J119.1, U40.4
INT40: J122.1, U41.4
INT41: J125.1, U42.4
INT42: J128.1, U43.4
INT43: J131.1, U44.4
INT44: J134.1, U45.4
INT45: J137.1, U46.4
INT46: J140.1, U47.4
INT47: J143.1, U48.4
INT48: J146.1, U49.4
INT49: J149.1, U50.4
INT50: J152.1, U51.4
INT51: J155.1, U52.4
INT52: J158.1, U53.4
INT53: J161.1, U54.4
INT54: J164.1, U55.4
INT55: J167.1, U56.4
INT56: J170.1, U57.4
INT57: J173.1, U58.4
INT58: J176.1, U59.4
INT59: J179.1, U60.4
INT60: J182.1, U61.4
INT61: J185.1, U62.4
INT62: J188.1, U63.4
INT63: J191.1, U64.4
unnamed: D1.C, R5.2
unnamed: I2C.3, R1.2
unnamed: I2C.1, R2.1
unnamed: D1.A, PWR.1
unnamed: ADR.3, R4.2
unnamed: ADR.1, R3.1
unnamed: I2C1.3, R6.2
unnamed: I2C1.1, R7.1
unnamed: ADR1.3, R9.2
unnamed: ADR1.1, R8.1
unnamed: D2.C, R10.2
unnamed: D2.A, PWR1.1
unnamed: I2C2.3, R11.2
unnamed: I2C2.1, R12.1
unnamed: ADR2.3, R14.2
unnamed: ADR2.1, R13.1
unnamed: D3.C, R15.2
unnamed: D3.A, PWR2.1
unnamed: I2C3.3, R16.2
unnamed: I2C3.1, R17.1
unnamed: ADR3.3, R19.2
unnamed: ADR3.1, R18.1
unnamed: D4.C, R20.2
unnamed: D4.A, PWR3.1
unnamed: I2C4.3, R21.2
unnamed: I2C4.1, R22.1
unnamed: ADR4.3, R24.2
unnamed: ADR4.1, R23.1
unnamed: D5.C, R25.2
unnamed: D5.A, PWR4.1
unnamed: I2C5.3, R26.2
unnamed: I2C5.1, R27.1
unnamed: ADR5.3, R29.2
unnamed: ADR5.1, R28.1
unnamed: D6.C, R30.2
unnamed: D6.A, PWR5.1
unnamed: I2C6.3, R31.2
unnamed: I2C6.1, R32.1
unnamed: ADR6.3, R34.2
unnamed: ADR6.1, R33.1
unnamed: D7.C, R35.2
unnamed: D7.A, PWR6.1
unnamed: I2C7.3, R36.2
unnamed: I2C7.1, R37.1
unnamed: ADR7.3, R39.2
unnamed: ADR7.1, R38.1
unnamed: D8.C, R40.2
unnamed: D8.A, PWR7.1
unnamed: I2C8.3, R41.2
unnamed: I2C8.1, R42.1
unnamed: ADR8.3, R44.2
unnamed: ADR8.1, R43.1
unnamed: D9.C, R45.2
unnamed: D9.A, PWR8.1
unnamed: I2C9.3, R46.2
unnamed: I2C9.1, R47.1
unnamed: ADR9.3, R49.2
unnamed: ADR9.1, R48.1
unnamed: D10.C, R50.2
unnamed: D10.A, PWR9.1
unnamed: I2C10.3, R51.2
unnamed: I2C10.1, R52.1
unnamed: ADR10.3, R54.2
unnamed: ADR10.1, R53.1
unnamed: D11.C, R55.2
unnamed: D11.A, PWR10.1
unnamed: I2C11.3, R56.2
unnamed: I2C11.1, R57.1
unnamed: ADR11.3, R59.2
unnamed: ADR11.1, R58.1
unnamed: D12.C, R60.2
unnamed: D12.A, PWR11.1
unnamed: I2C12.3, R61.2
unnamed: I2C12.1, R62.1
unnamed: ADR12.3, R64.2
unnamed: ADR12.1, R63.1
unnamed: D13.C, R65.2
unnamed: D13.A, PWR12.1
unnamed: I2C13.3, R66.2
unnamed: I2C13.1, R67.1
unnamed: ADR13.3, R69.2
unnamed: ADR13.1, R68.1
unnamed: D14.C, R70.2
unnamed: D14.A, PWR13.1
unnamed: I2C14.3, R71.2
unnamed: I2C14.1, R72.1
unnamed: ADR14.3, R74.2
unnamed: ADR14.1, R73.1
unnamed: D15.C, R75.2
unnamed: D15.A, PWR14.1
unnamed: I2C15.3, R76.2
unnamed: I2C15.1, R77.1
unnamed: ADR15.3, R79.2
unnamed: ADR15.1, R78.1
unnamed: D16.C, R80.2
unnamed: D16.A, PWR15.1
unnamed: I2C16.3, R81.2
unnamed: I2C16.1, R82.1
unnamed: ADR16.3, R84.2
unnamed: ADR16.1, R83.1
unnamed: D17.C, R85.2
unnamed: D17.A, PWR16.1
unnamed: I2C17.3, R86.2
unnamed: I2C17.1, R87.1
unnamed: ADR17.3, R89.2
unnamed: ADR17.1, R88.1
unnamed: D18.C, R90.2
unnamed: D18.A, PWR17.1
unnamed: I2C18.3, R91.2
unnamed: I2C18.1, R92.1
unnamed: ADR18.3, R94.2
unnamed: ADR18.1, R93.1
unnamed: D19.C, R95.2
unnamed: D19.A, PWR18.1
unnamed: I2C19.3, R96.2
unnamed: I2C19.1, R97.1
unnamed: ADR19.3, R99.2
unnamed: ADR19.1, R98.1
unnamed: D20.C, R100.2
unnamed: D20.A, PWR19.1
unnamed: I2C20.3, R101.2
unnamed: I2C20.1, R102.1
unnamed: ADR20.3, R104.2
unnamed: ADR20.1, R103.1
unnamed: D21.C, R105.2
unnamed: D21.A, PWR20.1
unnamed: I2C21.3, R106.2
unnamed: I2C21.1, R107.1
unnamed: ADR21.3, R109.2
unnamed: ADR21.1, R108.1
unnamed: D22.C, R110.2
unnamed: D22.A, PWR21.1
unnamed: I2C22.3, R111.2
unnamed: I2C22.1, R112.1
unnamed: ADR22.3, R114.2
unnamed: ADR22.1, R113.1
unnamed: D23.C, R115.2
unnamed: D23.A, PWR22.1
unnamed: I2C23.3, R116.2
unnamed: I2C23.1, R117.1
unnamed: ADR23.3, R119.2
unnamed: ADR23.1, R118.1
unnamed: D24.C, R120.2
unnamed: D24.A, PWR23.1
unnamed: I2C24.3, R121.2
unnamed: I2C24.1, R122.1
unnamed: ADR24.3, R124.2
unnamed: ADR24.1, R123.1
unnamed: D25.C, R125.2
unnamed: D25.A, PWR24.1
unnamed: I2C25.3, R126.2
unnamed: I2C25.1, R127.1
unnamed: ADR25.3, R129.2
unnamed: ADR25.1, R128.1
unnamed: D26.C, R130.2
unnamed: D26.A, PWR25.1
unnamed: I2C26.3, R131.2
unnamed: I2C26.1, R132.1
unnamed: ADR26.3, R134.2
unnamed: ADR26.1, R133.1
unnamed: D27.C, R135.2
unnamed: D27.A, PWR26.1
unnamed: I2C27.3, R136.2
unnamed: I2C27.1, R137.1
unnamed: ADR27.3, R139.2
unnamed: ADR27.1, R138.1
unnamed: D28.C, R140.2
unnamed: D28.A, PWR27.1
unnamed: I2C28.3, R141.2
unnamed: I2C28.1, R142.1
unnamed: ADR28.3, R144.2
unnamed: ADR28.1, R143.1
unnamed: D29.C, R145.2
unnamed: D29.A, PWR28.1
unnamed: I2C29.3, R146.2
unnamed: I2C29.1, R147.1
unnamed: ADR29.3, R149.2
unnamed: ADR29.1, R148.1
unnamed: D30.C, R150.2
unnamed: D30.A, PWR29.1
unnamed: I2C30.3, R151.2
unnamed: I2C30.1, R152.1
unnamed: ADR30.3, R154.2
unnamed: ADR30.1, R153.1
unnamed: D31.C, R155.2
unnamed: D31.A, PWR30.1
unnamed: I2C31.3, R156.2
unnamed: I2C31.1, R157.1
unnamed: ADR31.3, R159.2
unnamed: ADR31.1, R158.1
unnamed: D32.C, R160.2
unnamed: D32.A, PWR31.1
unnamed: I2C32.3, R161.2
unnamed: I2C32.1, R162.1
unnamed: ADR32.3, R164.2
unnamed: ADR32.1, R163.1
unnamed: D33.C, R165.2
unnamed: D33.A, PWR32.1
unnamed: I2C33.3, R166.2
unnamed: I2C33.1, R167.1
unnamed: ADR33.3, R169.2
unnamed: ADR33.1, R168.1
unnamed: D34.C, R170.2
unnamed: D34.A, PWR33.1
unnamed: I2C34.3, R171.2
unnamed: I2C34.1, R172.1
unnamed: ADR34.3, R174.2
unnamed: ADR34.1, R173.1
unnamed: D35.C, R175.2
unnamed: D35.A, PWR34.1
unnamed: I2C35.3, R176.2
unnamed: I2C35.1, R177.1
unnamed: ADR35.3, R179.2
unnamed: ADR35.1, R178.1
unnamed: D36.C, R180.2
unnamed: D36.A, PWR35.1
unnamed: I2C36.3, R181.2
unnamed: I2C36.1, R182.1
unnamed: ADR36.3, R184.2
unnamed: ADR36.1, R183.1
unnamed: D37.C, R185.2
unnamed: D37.A, PWR36.1
unnamed: I2C37.3, R186.2
unnamed: I2C37.1, R187.1
unnamed: ADR37.3, R189.2
unnamed: ADR37.1, R188.1
unnamed: D38.C, R190.2
unnamed: D38.A, PWR37.1
unnamed: I2C38.3, R191.2
unnamed: I2C38.1, R192.1
unnamed: ADR38.3, R194.2
unnamed: ADR38.1, R193.1
unnamed: D39.C, R195.2
unnamed: D39.A, PWR38.1
unnamed: I2C39.3, R196.2
unnamed: I2C39.1, R197.1
unnamed: ADR39.3, R199.2
unnamed: ADR39.1, R198.1
unnamed: D40.C, R200.2
unnamed: D40.A, PWR39.1
unnamed: I2C40.3, R201.2
unnamed: I2C40.1, R202.1
unnamed: ADR40.3, R204.2
unnamed: ADR40.1, R203.1
unnamed: D41.C, R205.2
unnamed: D41.A, PWR40.1
unnamed: I2C41.3, R206.2
unnamed: I2C41.1, R207.1
unnamed: ADR41.3, R209.2
unnamed: ADR41.1, R208.1
unnamed: D42.C, R210.2
unnamed: D42.A, PWR41.1
unnamed: I2C42.3, R211.2
unnamed: I2C42.1, R212.1
unnamed: ADR42.3, R214.2
unnamed: ADR42.1, R213.1
unnamed: D43.C, R215.2
unnamed: D43.A, PWR42.1
unnamed: I2C43.3, R216.2
unnamed: I2C43.1, R217.1
unnamed: ADR43.3, R219.2
unnamed: ADR43.1, R218.1
unnamed: D44.C, R220.2
unnamed: D44.A, PWR43.1
unnamed: I2C44.3, R221.2
unnamed: I2C44.1, R222.1
unnamed: ADR44.3, R224.2
unnamed: ADR44.1, R223.1
unnamed: D45.C, R225.2
unnamed: D45.A, PWR44.1
unnamed: I2C45.3, R226.2
unnamed: I2C45.1, R227.1
unnamed: ADR45.3, R229.2
unnamed: ADR45.1, R228.1
unnamed: D46.C, R230.2
unnamed: D46.A, PWR45.1
unnamed: I2C46.3, R231.2
unnamed: I2C46.1, R232.1
unnamed: ADR46.3, R234.2
unnamed: ADR46.1, R233.1
unnamed: D47.C, R235.2
unnamed: D47.A, PWR46.1
unnamed: I2C47.3, R236.2
unnamed: I2C47.1, R237.1
unnamed: ADR47.3, R239.2
unnamed: ADR47.1, R238.1
unnamed: D48.C, R240.2
unnamed: D48.A, PWR47.1
unnamed: I2C48.3, R241.2
unnamed: I2C48.1, R242.1
unnamed: ADR48.3, R244.2
unnamed: ADR48.1, R243.1
unnamed: D49.C, R245.2
unnamed: D49.A, PWR48.1
unnamed: I2C49.3, R246.2
unnamed: I2C49.1, R247.1
unnamed: ADR49.3, R249.2
unnamed: ADR49.1, R248.1
unnamed: D50.C, R250.2
unnamed: D50.A, PWR49.1
unnamed: I2C50.3, R251.2
unnamed: I2C50.1, R252.1
unnamed: ADR50.3, R254.2
unnamed: ADR50.1, R253.1
unnamed: D51.C, R255.2
unnamed: D51.A, PWR50.1
unnamed: I2C51.3, R256.2
unnamed: I2C51.1, R257.1
unnamed: ADR51.3, R259.2
unnamed: ADR51.1, R258.1
unnamed: D52.C, R260.2
unnamed: D52.A, PWR51.1
unnamed: I2C52.3, R261.2
unnamed: I2C52.1, R262.1
unnamed: ADR52.3, R264.2
unnamed: ADR52.1, R263.1
unnamed: D53.C, R265.2
unnamed: D53.A, PWR52.1
unnamed: I2C53.3, R266.2
unnamed: I2C53.1, R267.1
unnamed: ADR53.3, R269.2
unnamed: ADR53.1, R268.1
unnamed: D54.C, R270.2
unnamed: D54.A, PWR53.1
unnamed: I2C54.3, R271.2
unnamed: I2C54.1, R272.1
unnamed: ADR54.3, R274.2
unnamed: ADR54.1, R273.1
unnamed: D55.C, R275.2
unnamed: D55.A, PWR54.1
unnamed: I2C55.3, R276.2
unnamed: I2C55.1, R277.1
unnamed: ADR55.3, R279.2
unnamed: ADR55.1, R278.1
unnamed: D56.C, R280.2
unnamed: D56.A, PWR55.1
unnamed: I2C56.3, R281.2
unnamed: I2C56.1, R282.1
unnamed: ADR56.3, R284.2
unnamed: ADR56.1, R283.1
unnamed: D57.C, R285.2
unnamed: D57.A, PWR56.1
unnamed: I2C57.3, R286.2
unnamed: I2C57.1, R287.1
unnamed: ADR57.3, R289.2
unnamed: ADR57.1, R288.1
unnamed: D58.C, R290.2
unnamed: D58.A, PWR57.1
unnamed: I2C58.3, R291.2
unnamed: I2C58.1, R292.1
unnamed: ADR58.3, R294.2
unnamed: ADR58.1, R293.1
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
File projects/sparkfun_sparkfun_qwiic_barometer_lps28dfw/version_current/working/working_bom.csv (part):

"Id";"Designator";"Footprint";"Quantity";"Designation";"Supplier and ref";
1;"D37,D6,D12,D62,D18,D43,D52,D16,D60,D23,D53,D48,D10,D25,D7,D30,D36,D42,D44,D28,D19,D14,D34,D38,D20,D63,D1,D29,D45,D49,D15,D50,D3,D58,D9,D32,D13,D55,D51,D22,D46,D56,D2,D31,D40,D8,D17,D33,D57,D64,D35,D59,D26,D21,D54,D39,D47,D5,D11,D41,D61,D4,D24,D27";"LED-0402";64;"RED";;;
2;"J19,J13,J55,J118,J109,J79,J85,J175,J94,J70,J16,J76,J151,J169,J40,J127,J52,J100,J121,J148,J130,J10,J2,J82,J31,J166,J178,J46,J103,J61,J133,J88,J73,J22,J64,J34,J187,J163,J124,J157,J4,J106,J28,J145,J181,J7,J25,J190,J58,J97,J112,J91,J184,J43,J37,J67,J154,J139,J136,J172,J160,J49,J115,J142";"JST04_1MM_RA";64;"QWIIC_RIGHT_ANGLE";;;
3;"J150,J30,J20,J26,J177,J107,J102,J138,J101,J66,J117,J137,J171,J6,J87,J149,J111,J153,J144,J114,J176,J188,J44,J143,J21,J84,J86,J53,J50,J192,J185,J74,J158,J57,J12,J122,J162,J119,J78,J81,J62,J105,J147,J5,J141,J14,J146,J71,J51,J68,J17,J11,J38,J29,J104,J189,J152,J8,J155,J3,J135,J123,J45,J165,J48,J191,J120,J99,J35,J168,J69,J27,J89,J182,J173,J183,J42,J24,J83,J60,J33,J108,J77,J59,J15,J1,J180,J9,J39,J98,J75,J186,J156,J32,J41,J179,J129,J56,J131,J96,J116,J125,J132,J63,J54,J161,J113,J90,J128,J36,J65,J18,J159,J23,J92,J170,J47,J126,J110,J93,J164,J80,J72,J167,J95,J174,J140,J134";"1X01_1MM_NO_SILK";128;"";;;
4;"U$568,U$458,U$359,U$678,U$656,U$51,U$117,U$29,U$579,U$62,U$535,U$337,U$106,U$425,U$139,U$601,U$128,U$315,U$18,U$557,U$282,U$216,U$150,U$623,U$392,U$436,U$194,U$524,U$183,U$249,U$326,U$480,U$546,U$172,U$700,U$689,U$205,U$590,U$304,U$161,U$73,U$469,U$513,U$414,U$348,U$2,U$381,U$667,U$370,U$293,U$645,U$271,U$260,U$612,U$502,U$447,U$403,U$227,U$95,U$491,U$40,U$238,U$634,U$84,U$515,U$691,U$438,U$416,U$339,U$636,U$702,U$163,U$592,U$680,U$570,U$20,U$625,U$306,U$647,U$108,U$284,U$42,U$218,U$64,U$4,U$614,U$229,U$130,U$493,U$86,U$658,U$526,U$207,U$394,U$251,U$405,U$537,U$174,U$141,U$471,U$559,U$273,U$152,U$350,U$669,U$185,U$449,U$603,U$504,U$427,U$31,U$317,U$97,U$581,U$383,U$548,U$240,U$75,U$361,U$262,U$196,U$119,U$482,U$460,U$295,U$328,U$53,U$372";"#GND#0";128;"";;;
5;"U18,U47,U39,U7,U8,U57,U44,U12,U19,U58,U15,U28,U37,U22,U43,U29,U11,U24,U36,U45,U27,U10,U55,U61,U50,U26,U9,U34,U53,U49,U16,U1,U6,U23,U31,U2,U64,U17,U13,U62,U14,U32,U54,U60,U52,U4,U48,U56,U30,U25,U20,U41,U63,U3,U33,U42,U40,U5,U35,U51,U21,U59,U38,U46";"LPS28DFW";64;"LPS28DFW";;;
6;"LOGO141,LOGO63,LOGO51,LOGO12,LOGO3,LOGO57,LOGO192,LOGO174,LOGO108,LOGO114,LOGO69,LOGO54,LOGO159,LOGO144,LOGO102,LOGO15,LOGO33,LOGO180,LOGO150,LOGO186,LOGO138,LOGO105,LOGO81,LOGO78,LOGO123,LOGO42,LOGO120,LOGO99,LOGO129,LOGO24,LOGO72,LOGO39,LOGO90,LOGO153,LOGO117,LOGO93,LOGO111,LOGO18,LOGO189,LOGO36,LOGO87,LOGO171,LOGO60,LOGO45,LOGO66,LOGO48,LOGO6,LOGO177,LOGO147,LOGO168,LOGO30,LOGO27,LOGO75,LOGO162,LOGO126,LOGO132,LOGO21,LOGO165,LOGO156,LOGO183,LOGO135,LOGO96,LOGO9,LOGO84";"BLANK";64;"SFE_LOGO_NAME_FLAMEBLANK";;;
7;"H61,H22,H28,H60,H50,H11,H14,H44,H64,H37,H15,H54,H35,H52,H10,H47,H1,H31,H25,H63,H29,H27,H12,H13,H42,H59,H9,H56,H58,H39,H24,H48,H33,H57,H49,H7,H18,H23,H21,H2,H53,H38,H5,H34,H62,H43,H45,H6,H26,H16,H30,H17,H4,H19,H55,H3,H36,H41,H20,H40,H46,H51,H32,H8";"STAND-OFF";64;"STAND-OFF";;;
8;"FD14,FD180,FD28,FD220,FD78,FD122,FD234,FD218,FD222,FD156,FD244,FD192,FD44,FD98,FD214,FD38,FD184,FD212,FD224,FD232,FD142,FD110,FD204,FD124,FD132,FD170,FD52,FD50,FD6,FD20,FD162,FD12,FD100,FD112,FD114,FD120,FD146,FD54,FD240,FD94,FD136,FD84,FD62,FD148,FD4,FD46,FD182,FD172,FD18,FD254,FD144,FD118,FD88,FD64,FD66,FD202,FD198,FD60,FD140,FD126,FD72,FD168,FD26,FD164,FD248,FD188,FD190,FD256,FD230,FD216,FD76,FD152,FD16,FD48,FD104,FD106,FD236,FD92,FD40,FD116,FD90,FD82,FD96,FD68,FD186,FD206,FD128,FD34,FD194,FD250,FD42,FD22,FD150,FD102,FD134,FD108,FD80,FD242,FD238,FD226,FD246,FD36,FD70,FD174,FD86,FD252,FD130,FD30,FD178,FD10,FD154,FD200,FD2,FD32,FD176,FD160,FD208,FD210,FD56,FD196,FD58,FD138,FD166,FD74,FD158,FD228,FD24,FD8,FD131,FD221,FD105,FD9,FD99,FD247,FD29,FD155,FD117,FD173,FD175,FD161,FD71,FD49,FD3,FD17,FD147,FD47,FD135,FD193,FD163,FD133,FD97,FD123,FD101,FD129,FD69,FD197,FD119,FD55,FD33,FD57,FD157,FD83,FD137,FD65,FD185,FD139,FD63,FD169,FD67,FD235,FD195,FD85,FD205,FD229,FD227,FD243,FD201,FD143,FD125,FD27,FD239,FD7,FD75,FD107,FD191,FD225,FD59,FD89,FD21,FD255,FD145,FD45,FD171,FD81,FD39,FD93,FD151,FD115,FD113,FD251,FD233,FD219,FD159,FD121,FD5,FD111,FD91,FD35,FD249,FD241,FD253,FD223,FD61,FD77,FD217,FD177,FD31,FD187,FD41,FD189,FD181,FD19,FD213,FD73,FD87,FD23,FD1,FD43,FD167,FD37,FD237,FD207,FD95,FD53,FD183,FD245,FD141,FD209,FD103,FD231,FD51,FD25,FD13,FD15,FD211,FD179,FD11,FD203,FD149,FD199,FD79,FD127,FD109,FD215,FD165,FD153";"FIDUCIAL-MICRO";256;"FIDUCIALUFIDUCIAL";;;
9;"U$193,U$259,U$72,U$303,U$699,U$215,U$15,U$534,U$622,U$61,U$479,U$39,U$94,U$545,U$600,U$611,U$556,U$237,U$325,U$1,U$270,U$402,U$424,U$336,U$633,U$523,U$50,U$83,U$105,U$160,U$248,U$182,U$347,U$490,U$446,U$149,U$314,U$677,U$501,U$666,U$567,U$369,U$28,U$281,U$116,U$512,U$578,U$589,U$138,U$171,U$380,U$655,U$644,U$226,U$435,U$127,U$688,U$457,U$391,U$413,U$292,U$358,U$204,U$468,U$459,U$525,U$30,U$228,U$569,U$426,U$316,U$217,U$690,U$558,U$3,U$41,U$338,U$63,U$261,U$173,U$305,U$19,U$151,U$624,U$272,U$74,U$85,U$184,U$382,U$679,U$349,U$635,U$470,U$129,U$327,U$360,U$613,U$162,U$492,U$294,U$107,U$393,U$404,U$646,U$701,U$195,U$371,U$52,U$536,U$580,U$96,U$657,U$448,U$514,U$415,U$250,U$591,U$140,U$602,U$283,U$503,U$668,U$206,U$481,U$118,U$239,U$547,U$437";"#INT#0";128;"";;;
10;"R36,R41,R241,R285,R86,R71,R196,R236,R227,R187,R302,R62,R212,R107,R146,R6,R126,R40,R97,R160,R55,R161,R237,R290,R87,R15,R151,R210,R147,R191,R76,R82,R175,R185,R247,R261,R197,R150,R306,R96,R111,R216,R20,R195,R77,R200,R157,R316,R145,R266,R307,R81,R92,R230,R115,R317,R166,R296,R21,R186,R217,R232,R156,R251,R297,R250,R177,R215,R172,R70,R265,R206,R272,R90,R301,R207,R121,R165,R201,R260,R91,R85,R135,R2,R95,R35,R116,R245,R46,R132,R310,R292,R267,R311,R25,R56,R60,R171,R1,R282,R80,R291,R61,R181,R27,R22,R155,R105,R280,R235,R50,R231,R277,R101,R52,R240,R142,R182,R287,R10,R17,R5,R255,R315,R295,R222,R45,R305,R271,R26,R72,R167,R67,R137,R125,R257,R16,R152,R66,R176,R276,R170,R256,R275,R12,R106,R162,R312,R136,R127,R131,R102,R30,R281,R75,R226,R112,R140,R180,R47,R300,R122,R221,R270,R110,R211,R120,R262,R320,R51,R242,R130,R42,R190,R286,R32,R117,R31,R11,R192,R100,R37,R202,R205,R225,R220,R246,R57,R252,R141,R7,R65";"0402-TIGHT";192;"2.2k";;;
11;"U$527,U$450,U$142,U$461,U$274,U$230,U$131,U$648,U$373,U$549,U$32,U$98,U$615,U$21,U$483,U$604,U$582,U$252,U$593,U$428,U$670,U$494,U$703,U$560,U$571,U$417,U$219,U$120,U$5,U$681,U$439,U$351,U$109,U$43,U$285,U$186,U$164,U$65,U$659,U$153,U$241,U$329,U$76,U$307,U$626,U$538,U$87,U$175,U$395,U$197,U$362,U$637,U$406,U$296,U$208,U$505,U$472,U$692,U$263,U$318,U$54,U$516,U$384,U$340";"LPS28DFW0";64;"";;;
12;"R299,R128,R283,R89,R63,R79,R84,R48,R278,R198,R264,R149,R29,R169,R39,R308,R38,R64,R194,R104,R199,R53,R34,R78,R304,R58,R293,R144,R148,R158,R224,R114,R298,R229,R3,R74,R123,R184,R93,R204,R23,R139,R253,R174,R44,R98,R213,R119,R258,R209,R154,R9,R19,R59,R129,R168,R4,R263,R279,R103,R233,R69,R288,R219,R133,R188,R314,R134,R14,R83,R313,R8,R173,R163,R239,R99,R214,R49,R43,R244,R18,R223,R178,R259,R228,R28,R189,R24,R234,R183,R319,R68,R274,R88,R54,R159,R13,R153,R249,R118,R138,R164,R243,R309,R73,R109,R268,R33,R179,R318,R273,R303,R94,R218,R238,R269,R254,R248,R289,R284,R124,R113,R193,R208,R294,R203,R143,R108";"0402-TIGHT";128;"10k";;;
13;"C6,C16,C44,C2,C23,C41,C38,C47,C24,C35,C37,C59,C31,C54,C5,C33,C64,C29,C61,C22,C18,C50,C14,C57,C21,C12,C36,C17,C3,C60,C40,C34,C48,C58,C15,C52,C8,C10,C9,C51,C7,C63,C20,C39,C46,C62,C56,C27,C4,C19,C43,C11,C25,C53,C26,C30,C55,C1,C42,C28,C49,C32,C45,C13";"0402-TIGHT";64;"0.1uF";;;
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

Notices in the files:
parts and their libraries:
SparkFun-Aesthetics: Licensing: Creative Commons ShareAlike 4.0 International - https://creativecommons.org/licenses/by-sa/4.0
SparkFun-Aesthetics: Released under the Creative Commons Attribution Share-Alike 4.0 License
SparkFun-Aesthetics: https://creativecommons.org/licenses/by-sa/4.0
